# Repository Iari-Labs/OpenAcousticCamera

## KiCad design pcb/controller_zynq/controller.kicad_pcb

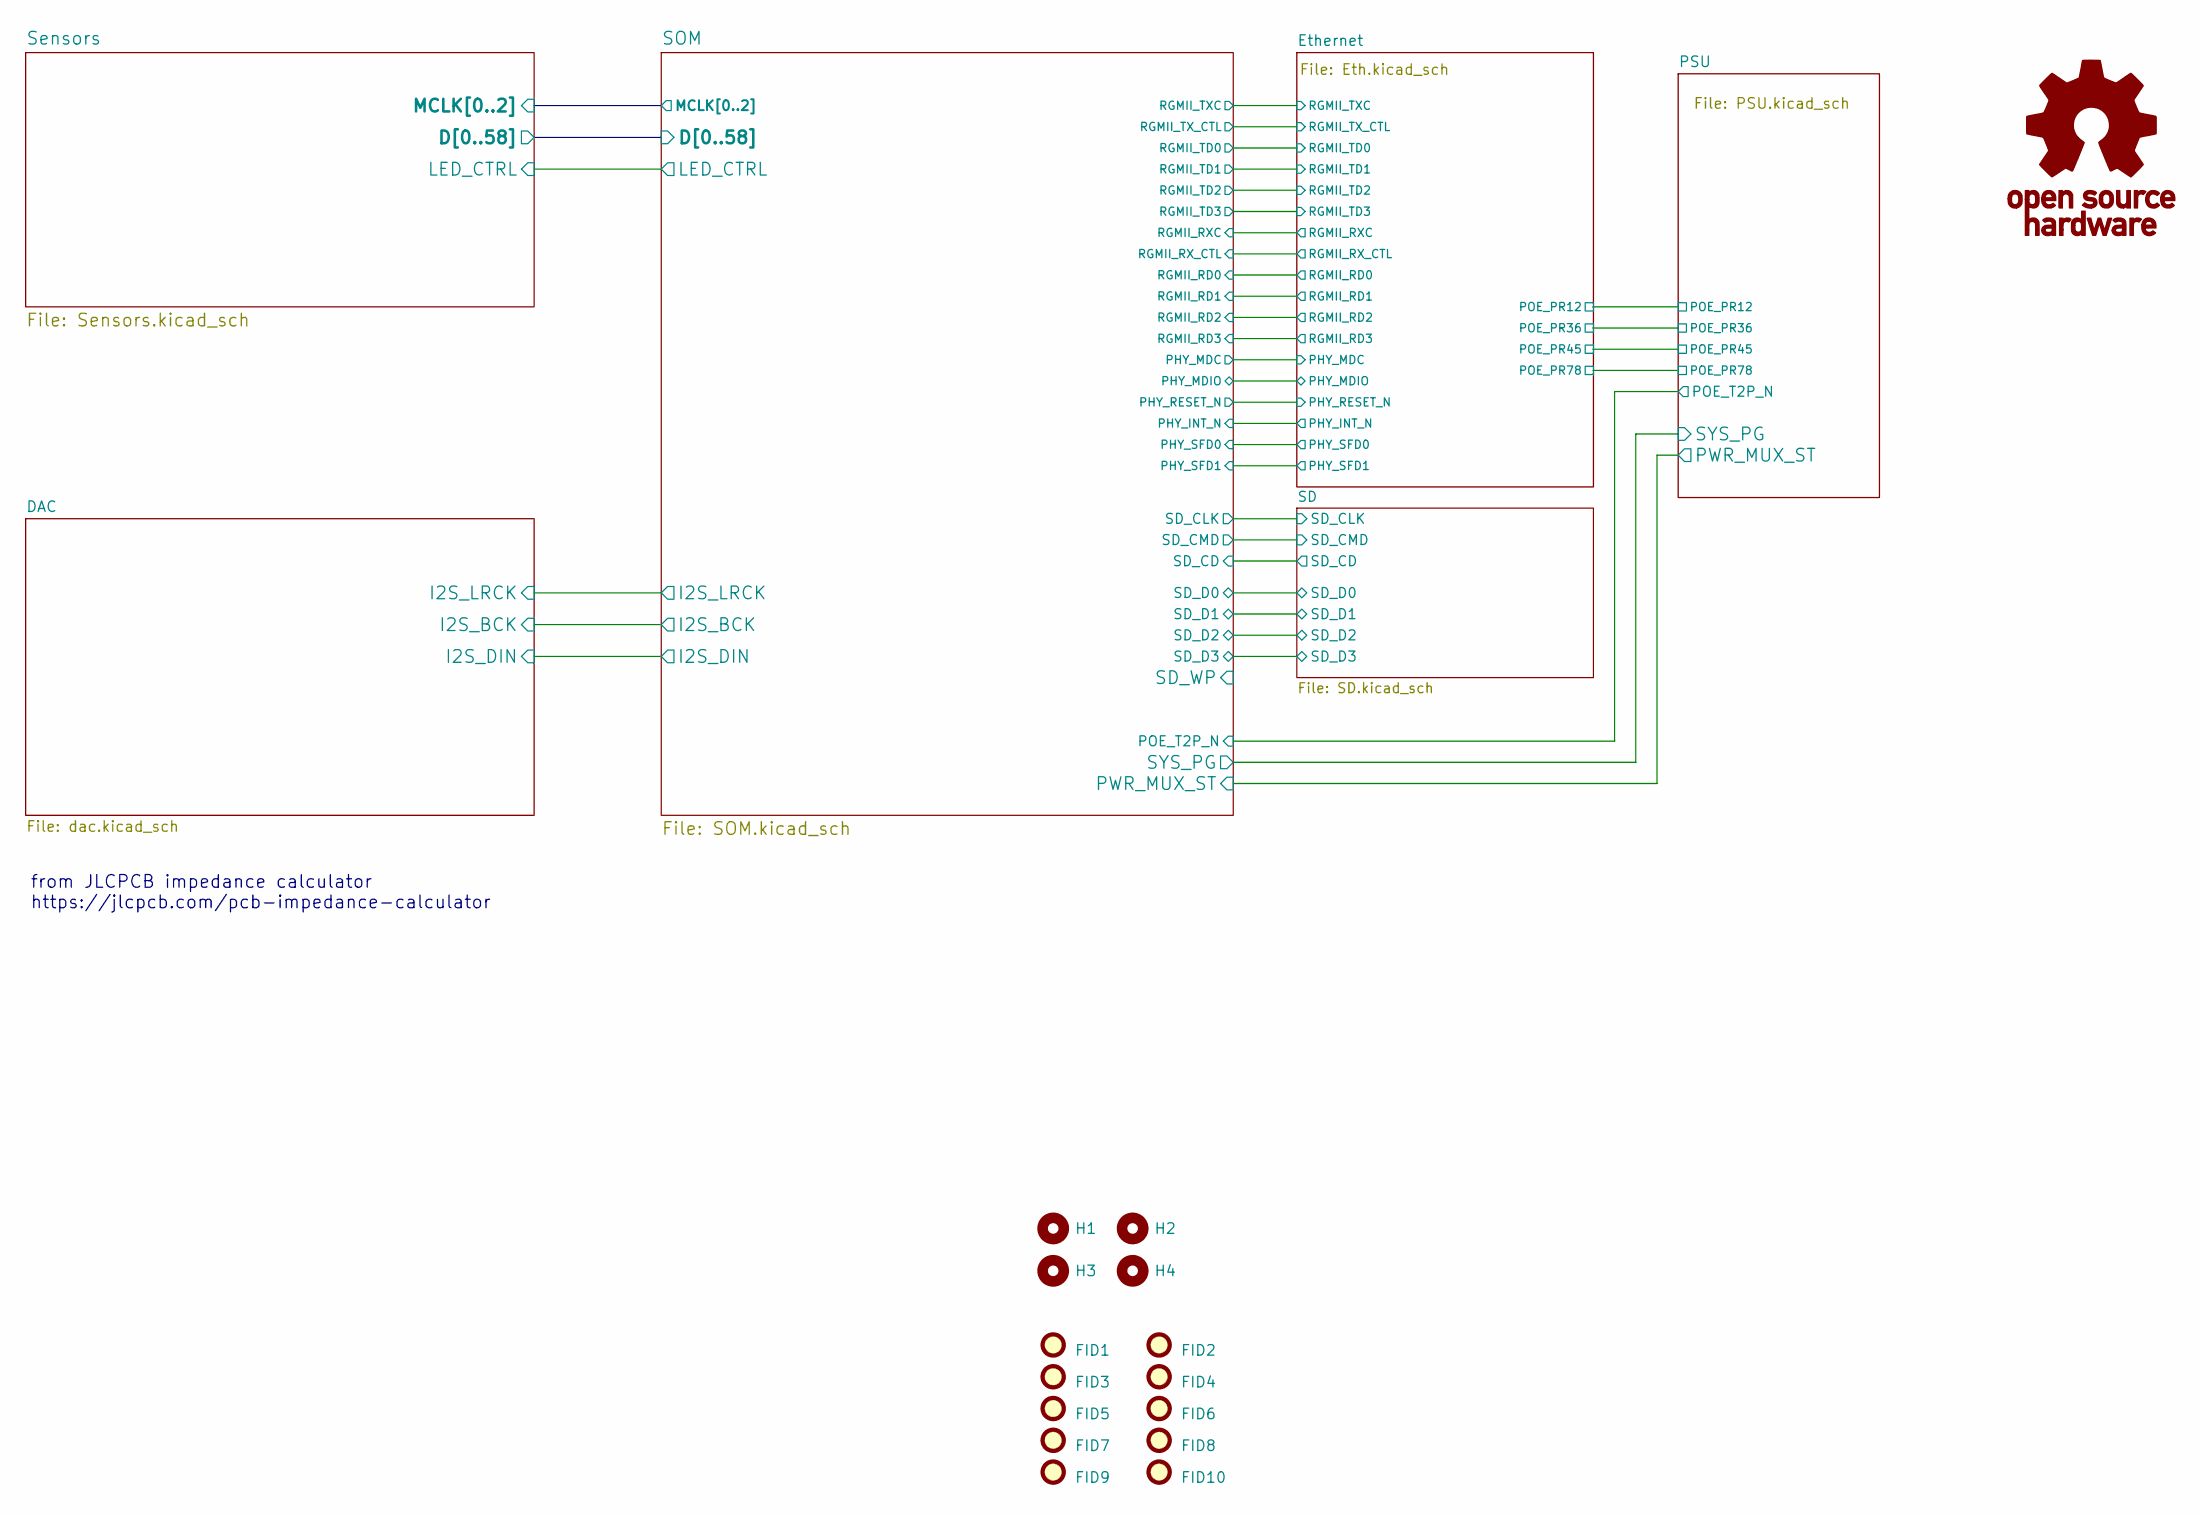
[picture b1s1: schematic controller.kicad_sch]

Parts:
FID1, FID2, FID3, FID4, FID5, FID6, FID7, FID8, FID9, FID10: Fiducial; Fiducial_0.5mm_Mask1mm
G1: LOGO; OSHW-Logo2_9.8x8mm_SilkScreen
H1, H2, H3, H4: MountingHole; MountingHole_3.7mm

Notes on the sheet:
from JLCPCB impedance calculator https://jlcpcb.com/pcb-impedance-calculator

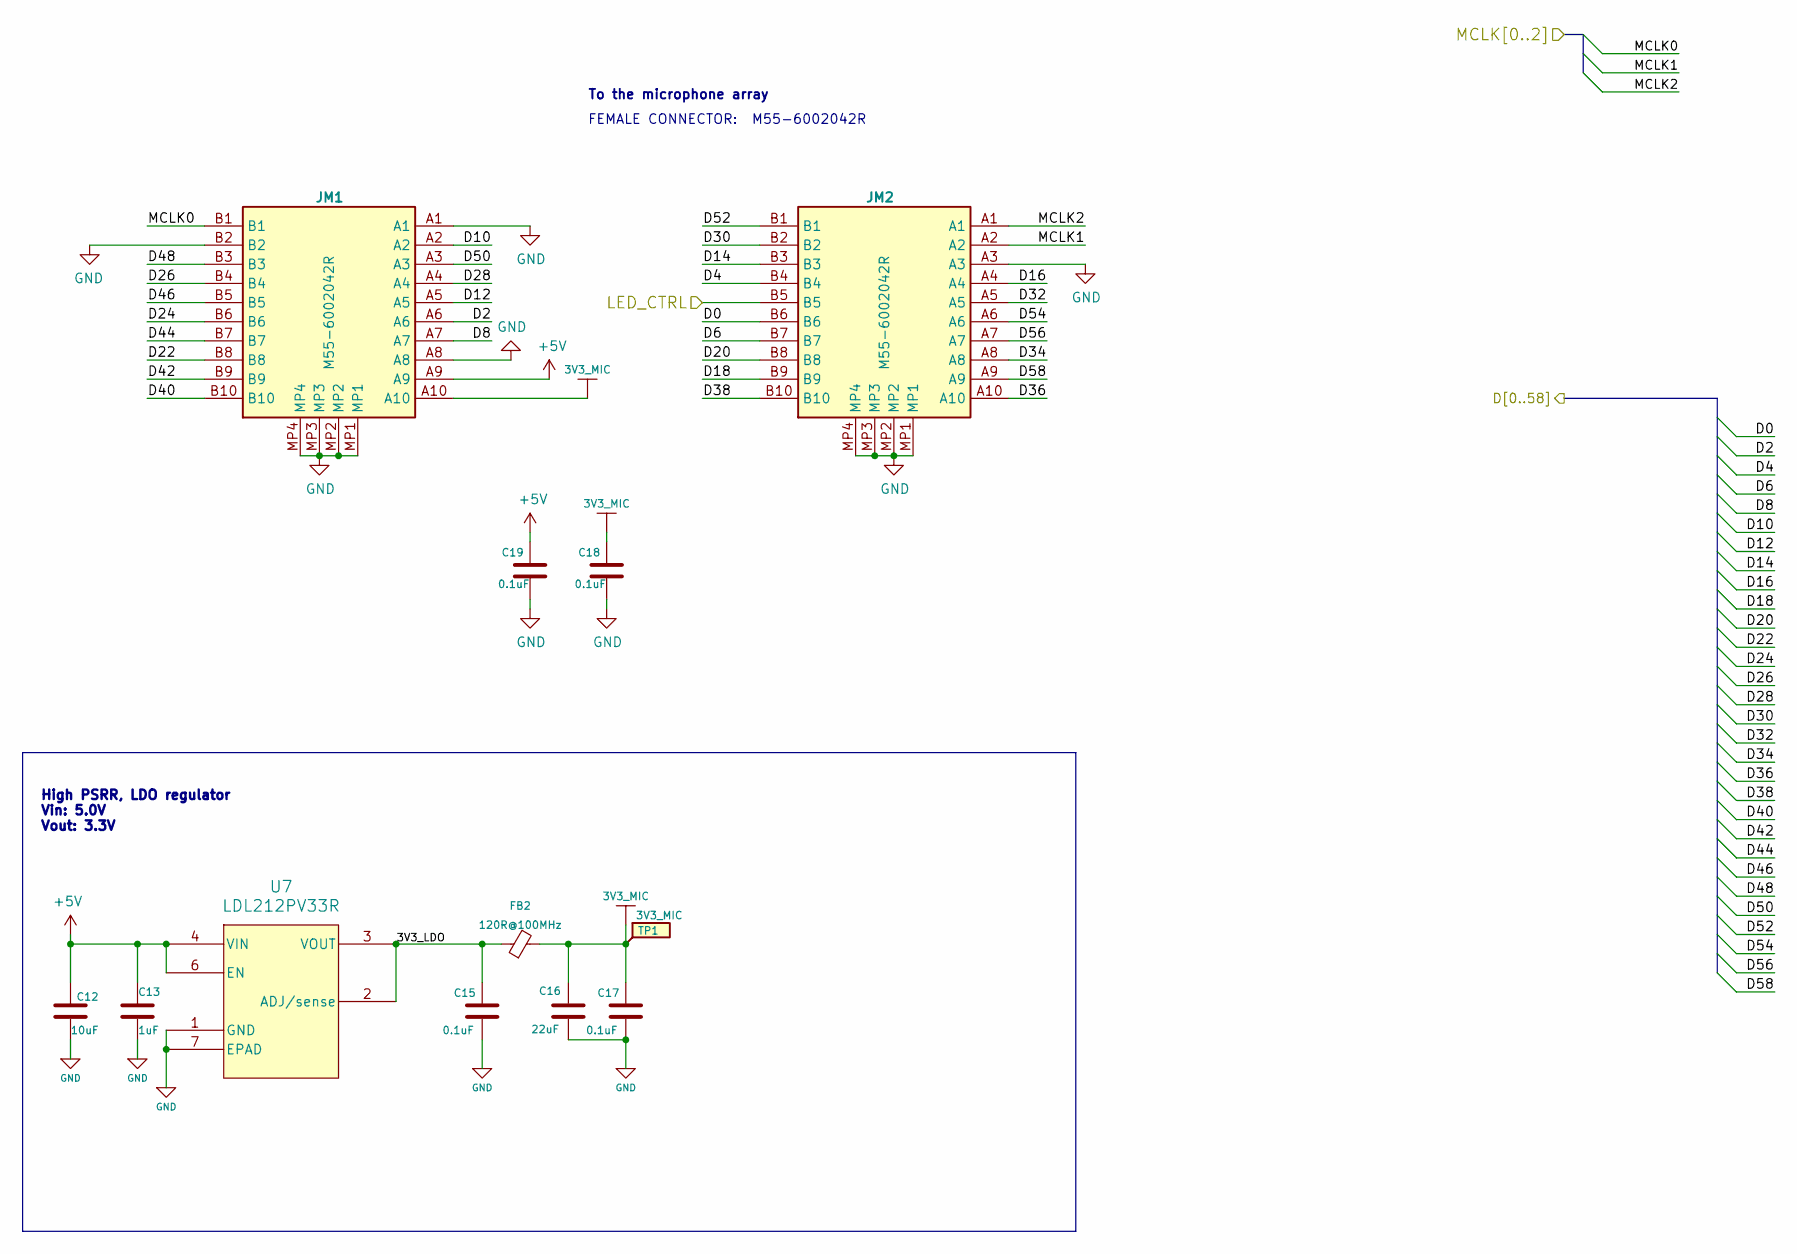
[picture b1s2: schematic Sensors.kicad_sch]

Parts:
C12: 10uF; C_0603_1608Metric; Manufacturer_Part_Number CL10A106KP8NNNC; Digikey Part Number 1276-6830-2-ND
C13: 1uF; C_0201_0603Metric; Manufacturer_Part_Number CL03A105MP3NSNC; Digikey Part Number 587-6278-2-ND
C15, C17, C18, C19: 0.1uF; C_0201_0603Metric; Manufacturer_Part_Number 0201X104K160NT; Digikey Part Number 587-3498-1-ND
C16: 22uF; C_0805_2012Metric; Manufacturer_Part_Number CL21A226MAQNNNE; Digikey Part Number 445-14428-1-ND
FB2: 120R@100MHz; L_0603_1608Metric; Manufacturer_Part_Number GZ1608D121TF; Digikey Part Number 553-BBUP00201209121Y00TR-ND
JM1, JM2: M55-6002042R; HARWIN_M55-6002042R; Manufacturer_Part_Number M55-7002042R; LCSC C6898669
TP1: 3V3_MIC; TestPoint_Pad_D1.0mm
U7: LDL212PV33R; DFN_V33R_STM; Manufacturer_Part_Number LDL212PV33R; LCSC C2969892

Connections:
3V3_MIC: C16.1, C17.1, C18.1, FB2.2, JM1.A10, TP1.1 (1_1)
+5V: C12.1, C13.1, C19.1, JM1.A9, U7.4 (VIN), U7.6 (EN); also elsewhere on the board
/SOM/D0: JM2.B6; also elsewhere on the board
/SOM/D2: JM1.A6; also elsewhere on the board
/SOM/D4: JM2.B4; also elsewhere on the board
/SOM/D6: JM2.B7; also elsewhere on the board
/SOM/D8: JM1.A7; also elsewhere on the board
/SOM/D10: JM1.A2; also elsewhere on the board
/SOM/D12: JM1.A5; also elsewhere on the board
/SOM/D14: JM2.B3; also elsewhere on the board
/SOM/D16: JM2.A4; also elsewhere on the board
/SOM/D18: JM2.B9; also elsewhere on the board
/SOM/D20: JM2.B8; also elsewhere on the board
/SOM/D22: JM1.B8; also elsewhere on the board
/SOM/D24: JM1.B6; also elsewhere on the board
/SOM/D26: JM1.B4; also elsewhere on the board
/SOM/D28: JM1.A4; also elsewhere on the board
/SOM/D30: JM2.B2; also elsewhere on the board
/SOM/D32: JM2.A5; also elsewhere on the board
/SOM/D34: JM2.A8; also elsewhere on the board
/SOM/D36: JM2.A10; also elsewhere on the board
/SOM/D38: JM2.B10; also elsewhere on the board
/SOM/D40: JM1.B10; also elsewhere on the board
/SOM/D42: JM1.B9; also elsewhere on the board
/SOM/D44: JM1.B7; also elsewhere on the board
/SOM/D46: JM1.B5; also elsewhere on the board
/SOM/D48: JM1.B3; also elsewhere on the board
/SOM/D50: JM1.A3; also elsewhere on the board
/SOM/D52: JM2.B1; also elsewhere on the board
/SOM/D54: JM2.A6; also elsewhere on the board
/SOM/D56: JM2.A7; also elsewhere on the board
/SOM/D58: JM2.A9; also elsewhere on the board
/SOM/LED_CTRL: JM2.B5; also elsewhere on the board
/SOM/MCLK0: JM1.B1; also elsewhere on the board
/SOM/MCLK1: JM2.A2; also elsewhere on the board
/SOM/MCLK2: JM2.A1; also elsewhere on the board
/Sensors/3V3_LDO: C15.1, FB2.1, U7.2 (ADJ/sense), U7.3 (VOUT)
GND: C12.2, C13.2, C15.2, C16.2, C17.2, C18.2, C19.2, JM1.A1, JM1.A8, JM1.B2, JM1.MP1, JM1.MP2, JM1.MP3, JM1.MP4, JM2.A3, JM2.MP1, JM2.MP2, JM2.MP3, JM2.MP4, U7.1 (GND), U7.7 (EPAD); also elsewhere on the board

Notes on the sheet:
To the microphone array
High PSRR, LDO regulator Vin: 5.0V Vout: 3.3V
FEMALE CONNECTOR: M55-6002042R

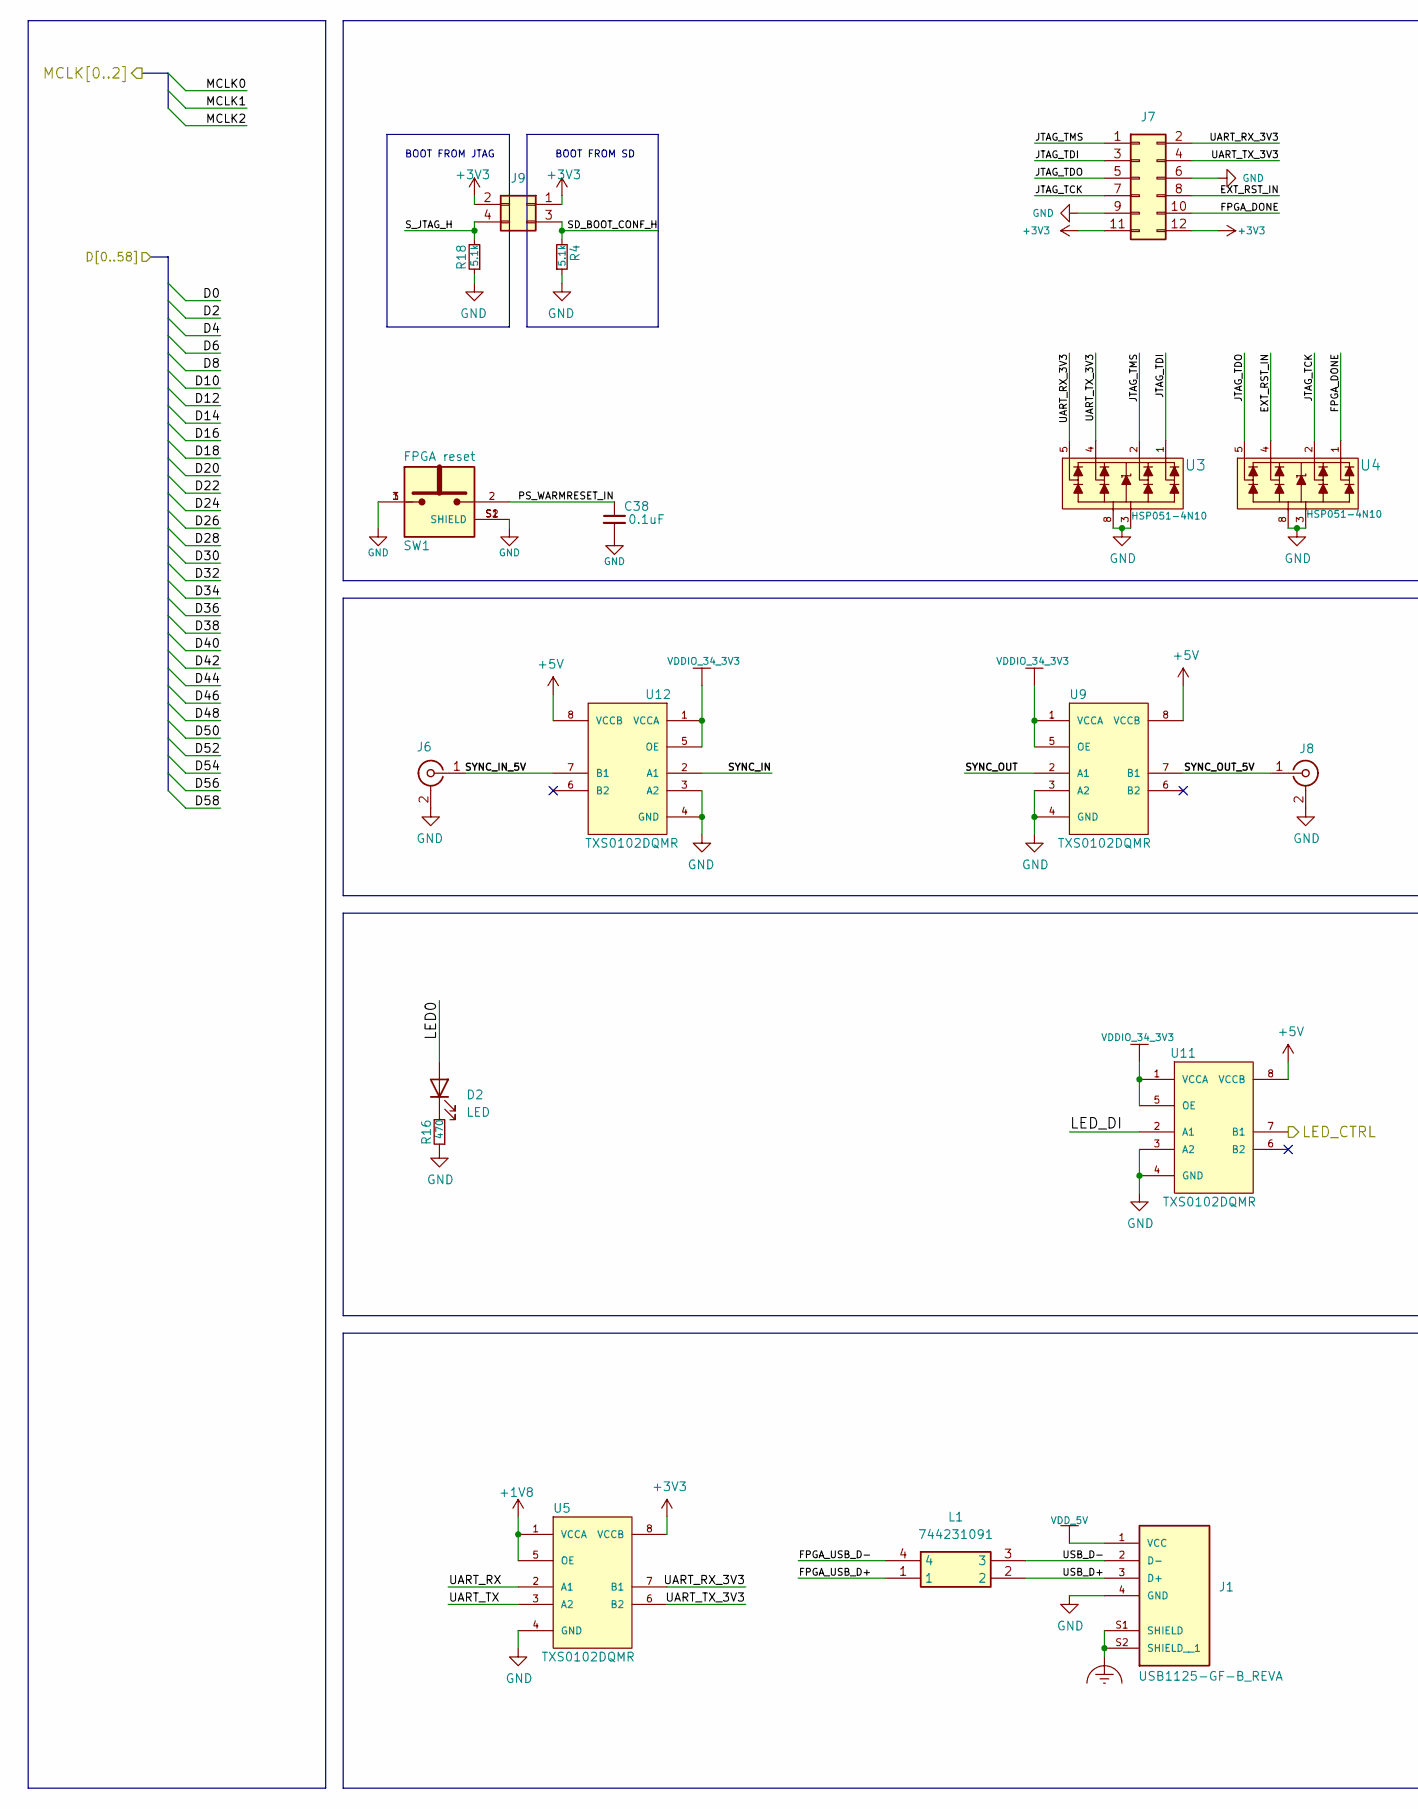
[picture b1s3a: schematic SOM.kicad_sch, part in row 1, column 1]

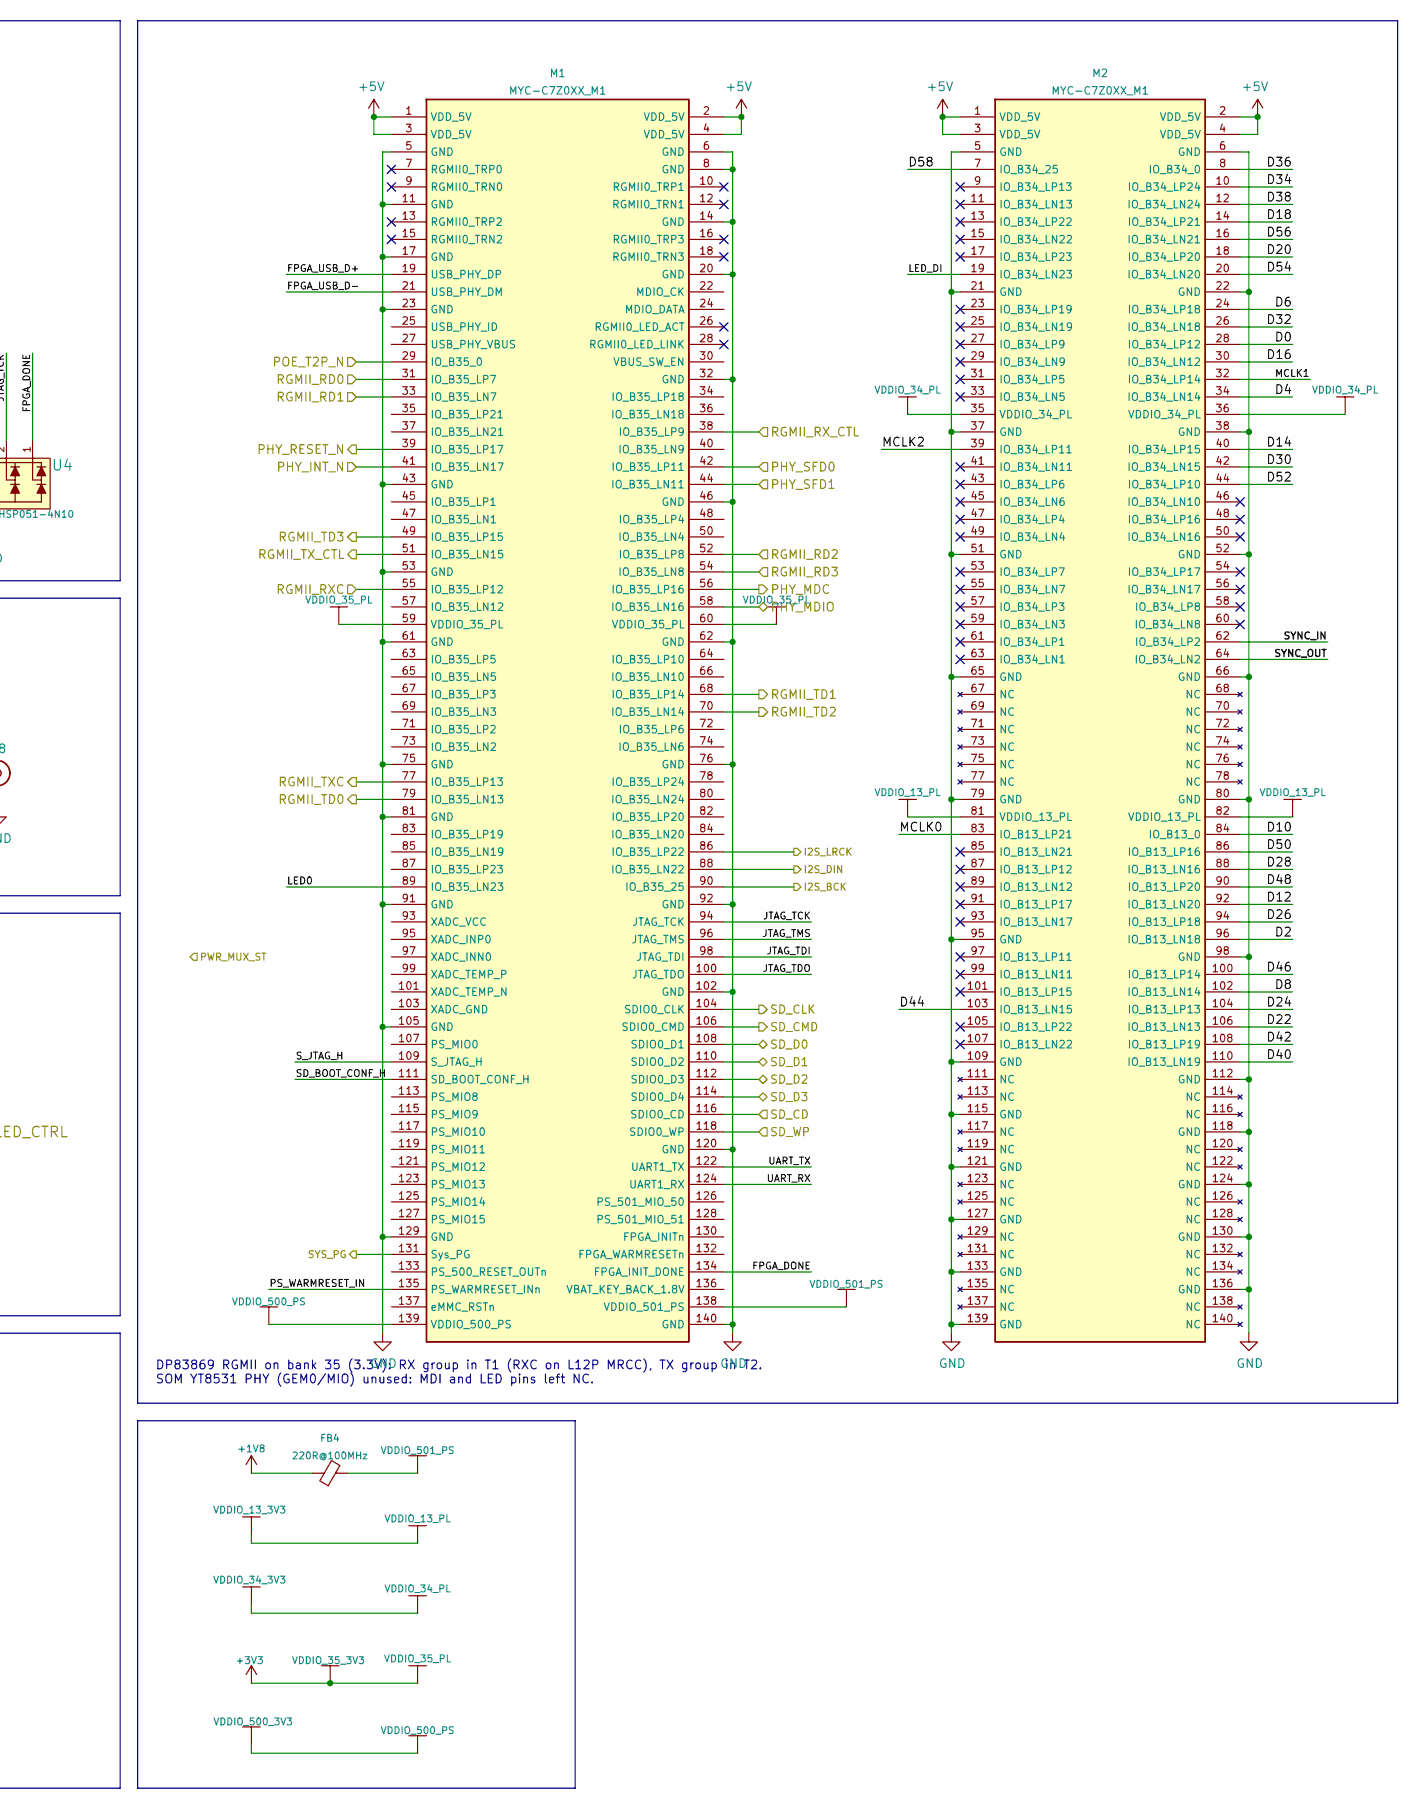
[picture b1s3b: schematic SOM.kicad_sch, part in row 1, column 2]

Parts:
C38: 0.1uF; C_0201_0603Metric; Manufacturer_Part_Number 0201X104K160NT; LCSC C2846674
D2: LED; LED_0402_1005Metric; Manufacturer_Part_Number A-SP136G2C-C01-3T; LCSC C5160718
FB4: 220R@100MHz; L_0603_1608Metric; Manufacturer_Part_Number GZ1608D221TF; Digikey Part Number 553-BBUP00201209121Y00TR-ND
J1: USB1125-GF-B_REVA; GCT_USB1125-GF-B_REVA; Manufacturer_Part_Number USB1125-GF-B; LCSC C5984324
J6, J8: CON-SMA-EDGE-S; RFSOLUTIONS_CON-SMA-EDGE-S; Manufacturer_Part_Number BWSMA-KE-P001; LCSC C496550
J7: 95278-101A12LF; PinHeader_2x06_P2.54mm_Vertical_SMD; LCSC C180404
J9: Conn_02x02_Odd_Even; PinHeader_2x02_P2.54mm_Vertical
L1: 744231091; WE-CNSW_08058; Manufacturer_Part_Number 744231091; LCSC C2649324
M1, M2: MYC-C7Z0XX_M1; 251779866; Manufacturer_Part_Number 2-5177986-6; LCSC C5163931
R4, R18: 5.1k; R_0201_0603Metric; Manufacturer_Part_Number ERJ-1GNJ512C; LCSC C270344
R16: 470; R_0402_1005Metric; Manufacturer_Part_Number 0402WGF470LTCE; LCSC C423162
SW1: FPGA reset; SW_SKRTLAE010; Manufacturer_Part_Number SKRTLAE010; Digikey Part Number 4809-SKRTLAE010CT-ND
U3, U4: HSP051-4N10; UQFN10_1P04X1P95X0P4_STM; Manufacturer_Part_Number HSP051-4N10; LCSC C2832770
U5, U9, U11, U12: TXS0102DQMR; IC_TXS0102DQMR; Manufacturer_Part_Number TXS0102DQMR; LCSC C108605

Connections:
+1V8: FB4.1, U5.1 (VCCA), U5.5 (OE); also elsewhere on the board
+3V3: J7.11, J7.12, J9.1, J9.2, M1.59 (VDDIO_35_PL), M1.60 (VDDIO_35_PL), U5.8 (VCCB); also elsewhere on the board
+5V: M1.1 (VDD_5V), M1.2 (VDD_5V), M1.3 (VDD_5V), M1.4 (VDD_5V), M2.1 (VDD_5V), M2.2 (VDD_5V), M2.3 (VDD_5V), M2.4 (VDD_5V), U9.8 (VCCB), U11.8 (VCCB), U12.8 (VCCB); also elsewhere on the board
/DAC/I2S_BCK: M1.90 (IO_B35_25); also elsewhere on the board
/DAC/I2S_DIN: M1.88 (IO_B35_LN22); also elsewhere on the board
/DAC/I2S_LRCK: M1.86 (IO_B35_LP22); also elsewhere on the board
/Ethernet/PHY_INT_N: M1.41 (IO_B35_LN17); also elsewhere on the board
/Ethernet/PHY_MDC: M1.56 (IO_B35_LP16); also elsewhere on the board
/Ethernet/PHY_MDIO: M1.58 (IO_B35_LN16); also elsewhere on the board
/Ethernet/PHY_RESET_N: M1.39 (IO_B35_LP17); also elsewhere on the board
/Ethernet/PHY_SFD0: M1.42 (IO_B35_LP11); also elsewhere on the board
/Ethernet/PHY_SFD1: M1.44 (IO_B35_LN11); also elsewhere on the board
/Ethernet/RGMII_RD0: M1.31 (IO_B35_LP7); also elsewhere on the board
/Ethernet/RGMII_RD1: M1.33 (IO_B35_LN7); also elsewhere on the board
/Ethernet/RGMII_RD2: M1.52 (IO_B35_LP8); also elsewhere on the board
/Ethernet/RGMII_RD3: M1.54 (IO_B35_LN8); also elsewhere on the board
/Ethernet/RGMII_RXC: M1.55 (IO_B35_LP12); also elsewhere on the board
/Ethernet/RGMII_RX_CTL: M1.38 (IO_B35_LP9); also elsewhere on the board
/Ethernet/RGMII_TD0: M1.79 (IO_B35_LN13); also elsewhere on the board
/Ethernet/RGMII_TD1: M1.68 (IO_B35_LP14); also elsewhere on the board
/Ethernet/RGMII_TD2: M1.70 (IO_B35_LN14); also elsewhere on the board
/Ethernet/RGMII_TD3: M1.49 (IO_B35_LP15); also elsewhere on the board
/Ethernet/RGMII_TXC: M1.77 (IO_B35_LP13); also elsewhere on the board
/Ethernet/RGMII_TX_CTL: M1.51 (IO_B35_LN15); also elsewhere on the board
/PSU/POE_T2P_N: M1.29 (IO_B35_0); also elsewhere on the board
/PSU/SYS_PG: M1.131 (Sys_PG); also elsewhere on the board
/SD/SD_CD: M1.116 (SDIO0_CD); also elsewhere on the board
/SD/SD_CLK: M1.104 (SDIO0_CLK); also elsewhere on the board
/SD/SD_CMD: M1.106 (SDIO0_CMD); also elsewhere on the board
/SD/SD_D0: M1.108 (SDIO0_D1); also elsewhere on the board
/SD/SD_D1: M1.110 (SDIO0_D2); also elsewhere on the board
/SD/SD_D2: M1.112 (SDIO0_D3); also elsewhere on the board
/SD/SD_D3: M1.114 (SDIO0_D4); also elsewhere on the board
/SOM/D0: M2.28 (IO_B34_LP12); also elsewhere on the board
/SOM/D2: M2.96 (IO_B13_LN18); also elsewhere on the board
/SOM/D4: M2.34 (IO_B34_LN14); also elsewhere on the board
/SOM/D6: M2.24 (IO_B34_LP18); also elsewhere on the board
/SOM/D8: M2.102 (IO_B13_LN14); also elsewhere on the board
/SOM/D10: M2.84 (IO_B13_0); also elsewhere on the board
/SOM/D12: M2.92 (IO_B13_LN20); also elsewhere on the board
/SOM/D14: M2.40 (IO_B34_LP15); also elsewhere on the board
/SOM/D16: M2.30 (IO_B34_LN12); also elsewhere on the board
/SOM/D18: M2.14 (IO_B34_LP21); also elsewhere on the board
/SOM/D20: M2.18 (IO_B34_LP20); also elsewhere on the board
/SOM/D22: M2.106 (IO_B13_LN13); also elsewhere on the board
/SOM/D24: M2.104 (IO_B13_LP13); also elsewhere on the board
/SOM/D26: M2.94 (IO_B13_LP18); also elsewhere on the board
/SOM/D28: M2.88 (IO_B13_LN16); also elsewhere on the board
/SOM/D30: M2.42 (IO_B34_LN15); also elsewhere on the board
/SOM/D32: M2.26 (IO_B34_LN18); also elsewhere on the board
/SOM/D34: M2.10 (IO_B34_LP24); also elsewhere on the board
/SOM/D36: M2.8 (IO_B34_0); also elsewhere on the board
/SOM/D38: M2.12 (IO_B34_LN24); also elsewhere on the board
/SOM/D40: M2.110 (IO_B13_LN19); also elsewhere on the board
/SOM/D42: M2.108 (IO_B13_LP19); also elsewhere on the board
/SOM/D44: M2.103 (IO_B13_LN15); also elsewhere on the board
/SOM/D46: M2.100 (IO_B13_LP14); also elsewhere on the board
/SOM/D48: M2.90 (IO_B13_LP20); also elsewhere on the board
/SOM/D50: M2.86 (IO_B13_LP16); also elsewhere on the board
/SOM/D52: M2.44 (IO_B34_LP10); also elsewhere on the board
/SOM/D54: M2.20 (IO_B34_LN20); also elsewhere on the board
/SOM/D56: M2.16 (IO_B34_LN21); also elsewhere on the board
/SOM/D58: M2.7 (IO_B34_25); also elsewhere on the board
/SOM/EXT_RST_IN: J7.8, U4.4
/SOM/FPGA_DONE: J7.10, M1.134 (FPGA_INIT_DONE), U4.1
/SOM/FPGA_USB_D+: L1.1, M1.19 (USB_PHY_DP)
/SOM/FPGA_USB_D-: L1.4, M1.21 (USB_PHY_DM)
/SOM/JTAG_TCK: J7.7, M1.94 (JTAG_TCK), U4.2
/SOM/JTAG_TDI: J7.3, M1.98 (JTAG_TDI), U3.1
/SOM/JTAG_TDO: J7.5, M1.100 (JTAG_TDO), U4.5
/SOM/JTAG_TMS: J7.1, M1.96 (JTAG_TMS), U3.2
/SOM/LED0: D2.2 (A), M1.89 (IO_B35_LN23)
/SOM/LED_CTRL: U11.7 (B1); also elsewhere on the board
/SOM/LED_DI: M2.19 (IO_B34_LN23), U11.2 (A1)
/SOM/MCLK0: M2.83 (IO_B13_LP21); also elsewhere on the board
/SOM/MCLK1: M2.32 (IO_B34_LP14); also elsewhere on the board
/SOM/MCLK2: M2.39 (IO_B34_LP11); also elsewhere on the board
/SOM/PS_WARMRESET_IN: C38.1, M1.135 (PS_WARMRESET_INn), SW1.2
/SOM/SD_BOOT_CONF_H: J9.3, M1.111 (SD_BOOT_CONF_H), R4.2
/SOM/SD_WP: M1.118 (SDIO0_WP)
/SOM/SYNC_IN: M2.62 (IO_B34_LP2), U12.2 (A1)
/SOM/SYNC_IN_5V: J6.1 (In), U12.7 (B1)
/SOM/SYNC_OUT: M2.64 (IO_B34_LN2), U9.2 (A1)
/SOM/SYNC_OUT_5V: J8.1 (In), U9.7 (B1)
/SOM/S_JTAG_H: J9.4, M1.109 (S_JTAG_H), R18.2
/SOM/UART_RX: M1.124 (UART1_RX), U5.2 (A1)
/SOM/UART_RX_3V3: J7.2, U3.5, U5.7 (B1)
/SOM/UART_TX: M1.122 (UART1_TX), U5.3 (A2)
/SOM/UART_TX_3V3: J7.4, U3.4, U5.6 (B2)
/SOM/USB_D+: J1.3 (D+), L1.2
/SOM/USB_D-: J1.2 (D-), L1.3
Earth_Clean: J1.S1 (SHIELD), J1.S2 (SHIELD__1); also elsewhere on the board
GND: C38.2, J1.4 (GND), J6.2 (Ext), J7.6, J7.9, J8.2 (Ext), M1.5 (GND), M1.6 (GND), M1.8 (GND), M1.11 (GND), M1.14 (GND), M1.17 (GND), M1.20 (GND), M1.23 (GND), M1.32 (GND), M1.43 (GND), M1.46 (GND), M1.53 (GND), M1.61 (GND), M1.62 (GND), M1.75 (GND), M1.76 (GND), M1.81 (GND), M1.91 (GND), M1.92 (GND), M1.102 (GND), M1.105 (GND), M1.120 (GND), M1.129 (GND), M1.140 (GND), M2.5 (GND), M2.6 (GND), M2.21 (GND), M2.22 (GND), M2.37 (GND), M2.38 (GND), M2.51 (GND), M2.52 (GND), M2.65 (GND), M2.66 (GND), M2.79 (GND), M2.80 (GND), M2.95 (GND), M2.98 (GND), M2.109 (GND), M2.112 (GND), M2.115 (GND), M2.118 (GND), M2.121 (GND), M2.124 (GND), M2.127 (GND), M2.130 (GND), M2.133 (GND), M2.136 (GND), M2.139 (GND), R4.1, R16.1, R18.1, SW1.1, SW1.3, SW1.S1 (SHIELD), SW1.S2 (SHIELD), U3.3, U3.8, U4.3, U4.8, U5.4 (GND), U9.3 (A2), U9.4 (GND), U11.3 (A2), U11.4 (GND), U12.3 (A2), U12.4 (GND); also elsewhere on the board
unnamed: D2.1 (K), R16.2
VDDIO_13_3V3: M2.81 (VDDIO_13_PL), M2.82 (VDDIO_13_PL)
VDDIO_34_3V3: M2.35 (VDDIO_34_PL), M2.36 (VDDIO_34_PL), U9.1 (VCCA), U9.5 (OE), U11.1 (VCCA), U11.5 (OE), U12.1 (VCCA), U12.5 (OE)
VDDIO_500_3V3: M1.139 (VDDIO_500_PS)
VDDIO_501_PS: FB4.2, M1.138 (VDDIO_501_PS)
VDD_5V: J1.1 (VCC)

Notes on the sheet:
DP83869 RGMII on bank 35 (3.3V): RX group in T1 (RXC on L12P MRCC), TX group in T2. SOM YT8531 PHY (GEM0/MIO) unused: MDI and LED pins left NC.
BOOT FROM JTAG
BOOT FROM SD

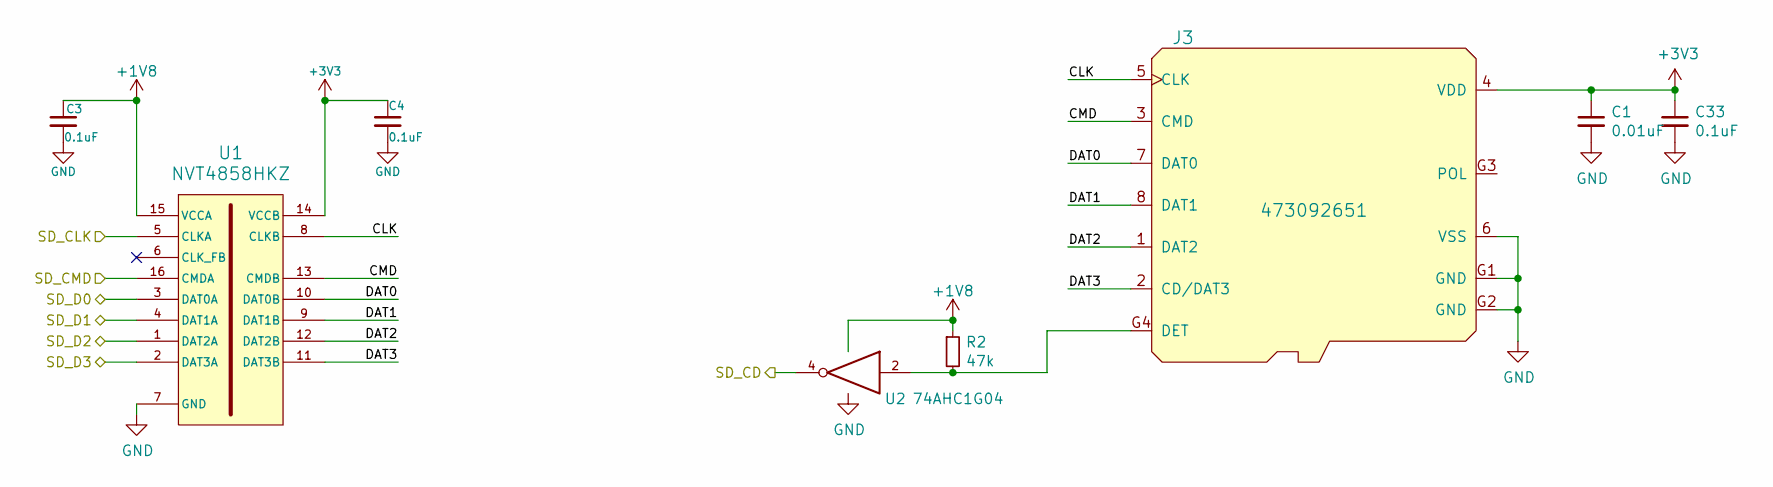
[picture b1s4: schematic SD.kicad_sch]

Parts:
C1: 0.01uF; C_0201_0603Metric; Manufacturer_Part_Number CL03A104KQ3NNNC; LCSC C285010
C3, C4, C33: 0.1uF; C_0201_0603Metric; Manufacturer_Part_Number 0201X104K160NT; LCSC C2846674
J3: 473092651; 0473093351; Manufacturer_Part_Number 473092651; LCSC C587826
R2: 47k; R_0201_0603Metric; Manufacturer_Part_Number 1GNF4702C; LCSC C270345
U1: NVT4858HKZ; NVT4858_NXP; Manufacturer_Part_Number NVT4858HKZ; LCSC C3035811
U2: 74AHC1G04; SOT-353_SC-70-5; Manufacturer_Part_Number 74AHC1G04SE-7; LCSC C460485

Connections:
+1V8: C3.1, R2.1, U1.15 (VCCA), U2.5 (VCC); also elsewhere on the board
+3V3: C1.1, C4.1, C33.1, J3.4 (VDD), U1.14 (VCCB); also elsewhere on the board
/SD/CLK: J3.5 (CLK), U1.8 (CLKB)
/SD/CMD: J3.3 (CMD), U1.13 (CMDB)
/SD/DAT0: J3.7 (DAT0), U1.10 (DAT0B)
/SD/DAT1: J3.8 (DAT1), U1.9 (DAT1B)
/SD/DAT2: J3.1 (DAT2), U1.12 (DAT2B)
/SD/DAT3: J3.2 (CD/DAT3), U1.11 (DAT3B)
/SD/SD_CD: U2.4; also elsewhere on the board
/SD/SD_CLK: U1.5 (CLKA); also elsewhere on the board
/SD/SD_CMD: U1.16 (CMDA); also elsewhere on the board
/SD/SD_D0: U1.3 (DAT0A); also elsewhere on the board
/SD/SD_D1: U1.4 (DAT1A); also elsewhere on the board
/SD/SD_D2: U1.1 (DAT2A); also elsewhere on the board
/SD/SD_D3: U1.2 (DAT3A); also elsewhere on the board
GND: C1.2, C3.2, C4.2, C33.2, J3.6 (VSS), J3.G1 (GND), J3.G2 (GND), U1.7 (GND), U2.3 (GND); also elsewhere on the board
unnamed: J3.G4 (DET), R2.2, U2.2
